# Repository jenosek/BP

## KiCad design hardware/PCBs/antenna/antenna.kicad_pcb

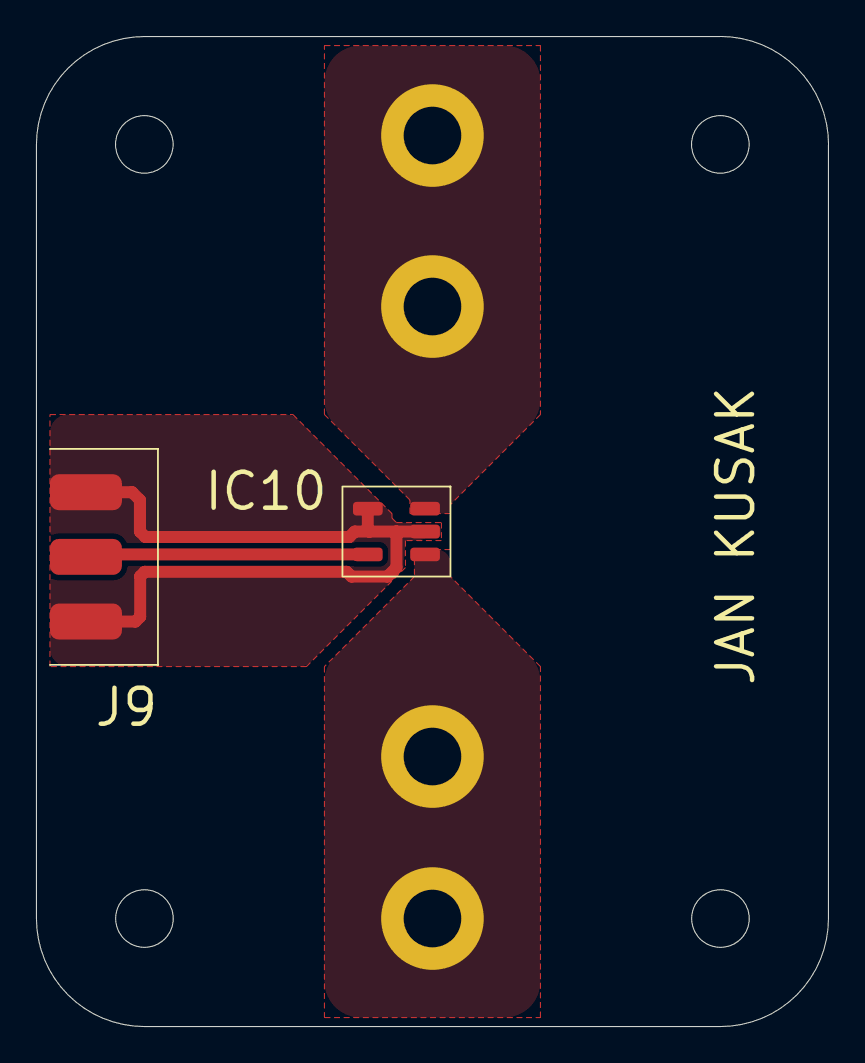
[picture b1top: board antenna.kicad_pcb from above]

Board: 2 copper layers, 44.0 x 55.0 mm, 10 parts (0 on the bottom side), 4 nets.

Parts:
H, H5, H6, H8: MountingHole; MountingHole_3.2mm_M3
H1, H2, H3, H4: MountingHole_Pad; MountingHole_3.2mm_M3_ISO7380_Pad
IC10: C1.5-52T+
J9: sma_diagonal

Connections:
GND: IC10.2 (SECONDARY_CT), IC10.4 (PRIMARY), J9.1 (GND), J9.3 (GND)
unnamed: IC10.6 (PRIMARY_DOT), J9.2 (SIGNAL)
unnamed: H3.1, H4.1, IC10.3 (SECONDARY)
unnamed: H1.1, H2.1, IC10.1 (SECONDARY_DOT)

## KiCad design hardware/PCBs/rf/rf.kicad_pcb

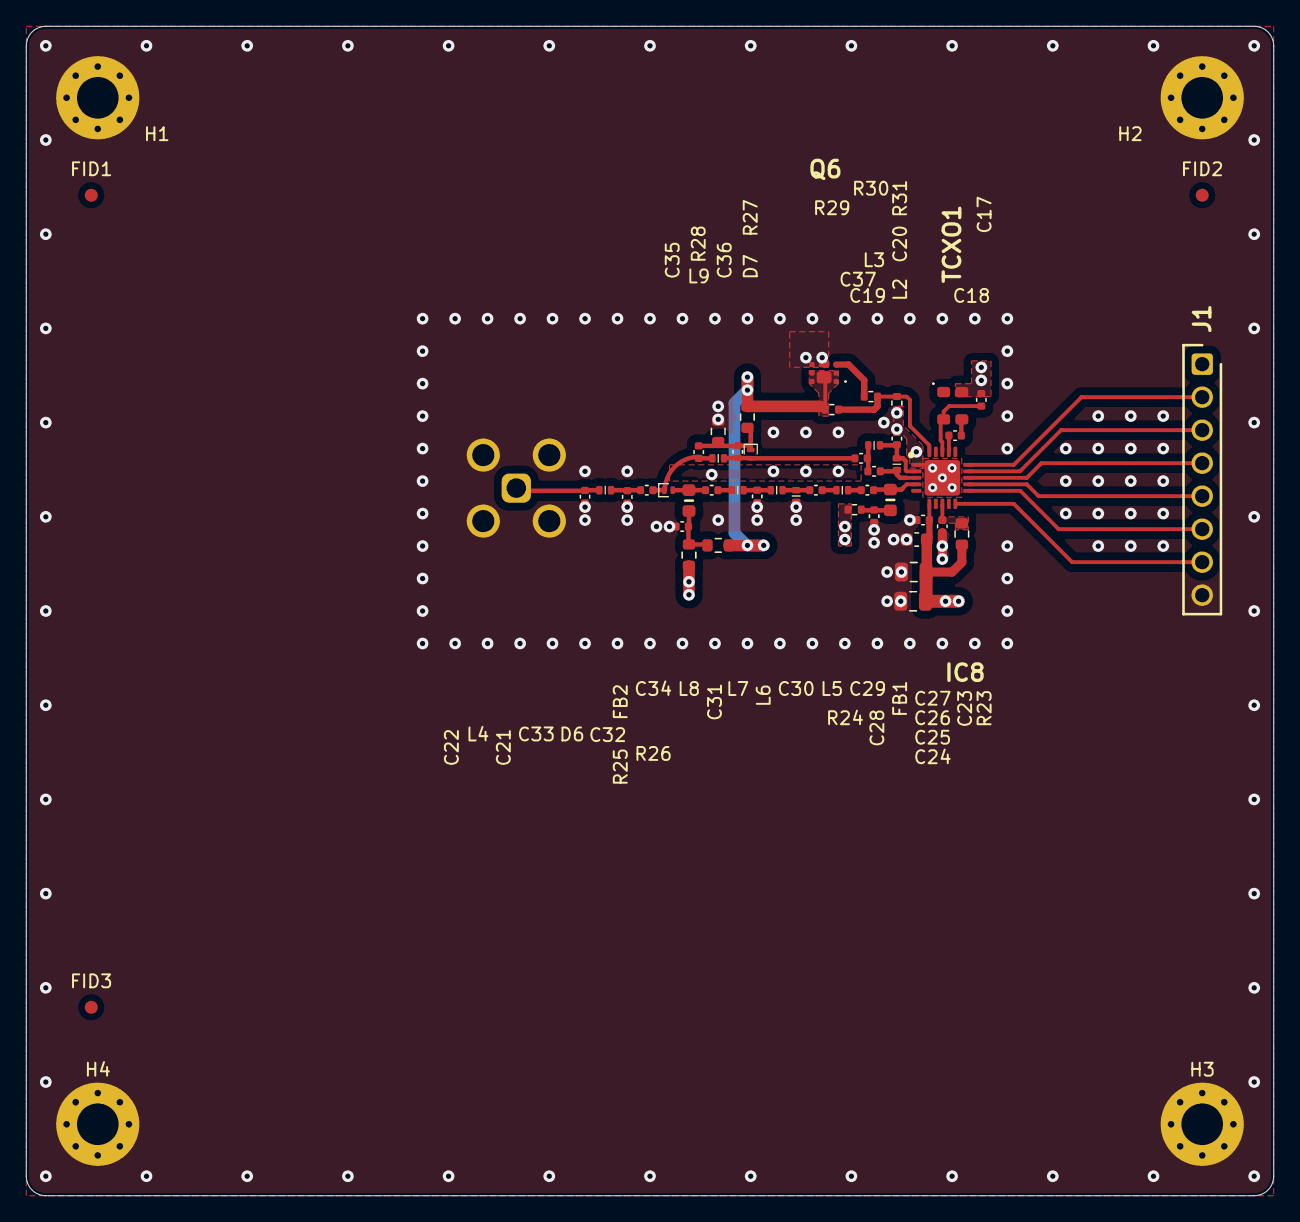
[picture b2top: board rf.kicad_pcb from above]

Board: 4 copper layers, 96.0 x 90.0 mm, 54 parts (1 on the bottom side), 32 nets.

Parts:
C17, C28, C32: 10n; C_0402_1005Metric
C18: 100p; C_0402_1005Metric
C19: 2p2; C_0402_1005Metric
C20: 4p7; C_0402_1005Metric
C21, C22, C35, C36: 8p8; C_0402_1005Metric
C23: 100n; C_0402_1005Metric
C24: 2u2; C_0805_2012Metric
C25: 100n; C_0805_2012Metric
C26: 100p; C_0603_1608Metric
C27: 33p; C_0402_1005Metric
C29: 7p5; C_0402_1005Metric
C30: 6p5; C_0402_1005Metric
C31: 7p3; C_0402_1005Metric
C33, C34, C37: 1n; C_0402_1005Metric
D6, D7: BAR63-02L-E6327; BAR6302LE6327
FB1, FB2: MMZ1608D241CTA00; BEADC1608X95N
FID1, FID2, FID3: Fiducial; Fiducial_1mm_Mask2mm
H1, H2, H3, H4: MountingHole_Pad; MountingHole_3.2mm_M3_Pad_Via
IC8: SI4468-A2A-IMR; QFN50P400X400X90-21N
J1: PH1-08-UA; HDRV8W64P0X254_1X8_2032X250X888P
J5: RFPC-SMA28-F; RFPCSMA28F
L2: 62n; LQW15CNR20J00B
L3: 56n; LQW15CNR20J00B
L4, L5, L9: 18n; LQW15CNR20J00B
L6, L7, L8: 20n; LQW15CNR20J00B
Q6: DMN1008UFDF-7; DMN1008UFDF7
R23, R26, R27, R28: 0; R_0603_1608Metric
R24: 178; R_0402_1005Metric
R25: 330; R_0603_1608Metric
R29, R30: 665; R_0402_1005Metric
R31: 100k; R_0402_1005Metric
TCXO1: TG2520SMN_30.000M-MCGNNM0; TG2520SMN30000MMCGNNM0

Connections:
+3V3: C17.1, C24.1, C25.1, C26.1, C27.1, IC8.6 (VDD_1), J1.1, R23.1, R24.1, R25.1, TCXO1.4 (VCC)
/ANT: C21.1, C33.1, L4.1
/COMMAND_DONE_RF: IC8.10 (GPIO1), J1.7
/GNDX: C17.2, IC8.18 (GND_1), TCXO1.2 (GND)
/Rx+: C20.2, IC8.2 (RXP), L2.2, L3.1
/Rx-: C19.1, IC8.3 (RXN), L2.1
/SCLK_RF: IC8.12 (SCLK), J1.5
/SDI_RF: IC8.14 (SDI), J1.3
/SDO_RF: IC8.13 (SDO), J1.4
/SW: Q6.1 (DRAIN_1), Q6.2 (DRAIN_2), Q6.5 (DRAIN_3), Q6.6 (DRAIN_4), Q6.7 (DRAIN_5), R26.1, R27.2, R29.1
/SW_MOS: IC8.20 (GPIO3), R29.2, R30.1, R31.1
/SW_Rx: C19.2, C37.2, L3.2
/SW_Tx: C34.2, L8.2
/Tx: C29.1, FB1.2, IC8.4 (TX)
/VDD2: C23.1, IC8.8 (VDD_2), R23.2
/XIN: C18.2, IC8.17 (XIN)
/nIRQ_RF: IC8.11 (NIRQ), J1.6
/nSEL_RF: IC8.15 (NSEL), J1.2
GND: C20.1, C21.2, C22.2, C23.2, C24.2, C25.2, C26.2, C27.2, C28.1, C31.1, C32.2, H1.1, H2.1, H3.1, H4.1, IC8.1 (SDN), IC8.21 (GND_2), J1.8, J5.2, J5.3, J5.4, J5.5, L6.2, Q6.4 (SOURCE_1), Q6.8 (SOURCE_2), R28.1, R31.2
unnamed: C22.1, J5.1, L4.2
unnamed: C28.2, FB1.1, R24.2
unnamed: C29.2, L5.1
unnamed: C30.1, L5.2
unnamed: C30.2, L6.1, L7.1
unnamed: C31.2, L7.2, L8.1
unnamed: C32.1, FB2.1, R25.2, R26.2
unnamed: C34.1, D6.2 (A), FB2.2
unnamed: C33.2, C35.1, D6.1 (K), L9.1
unnamed: C36.1, C37.1, D7.2 (A), L9.2
unnamed: C35.2, C36.2, D7.1 (K), R27.1, R28.2
unnamed: Q6.3 (GATE), R30.2
unnamed: C18.1, TCXO1.3 (OUT)

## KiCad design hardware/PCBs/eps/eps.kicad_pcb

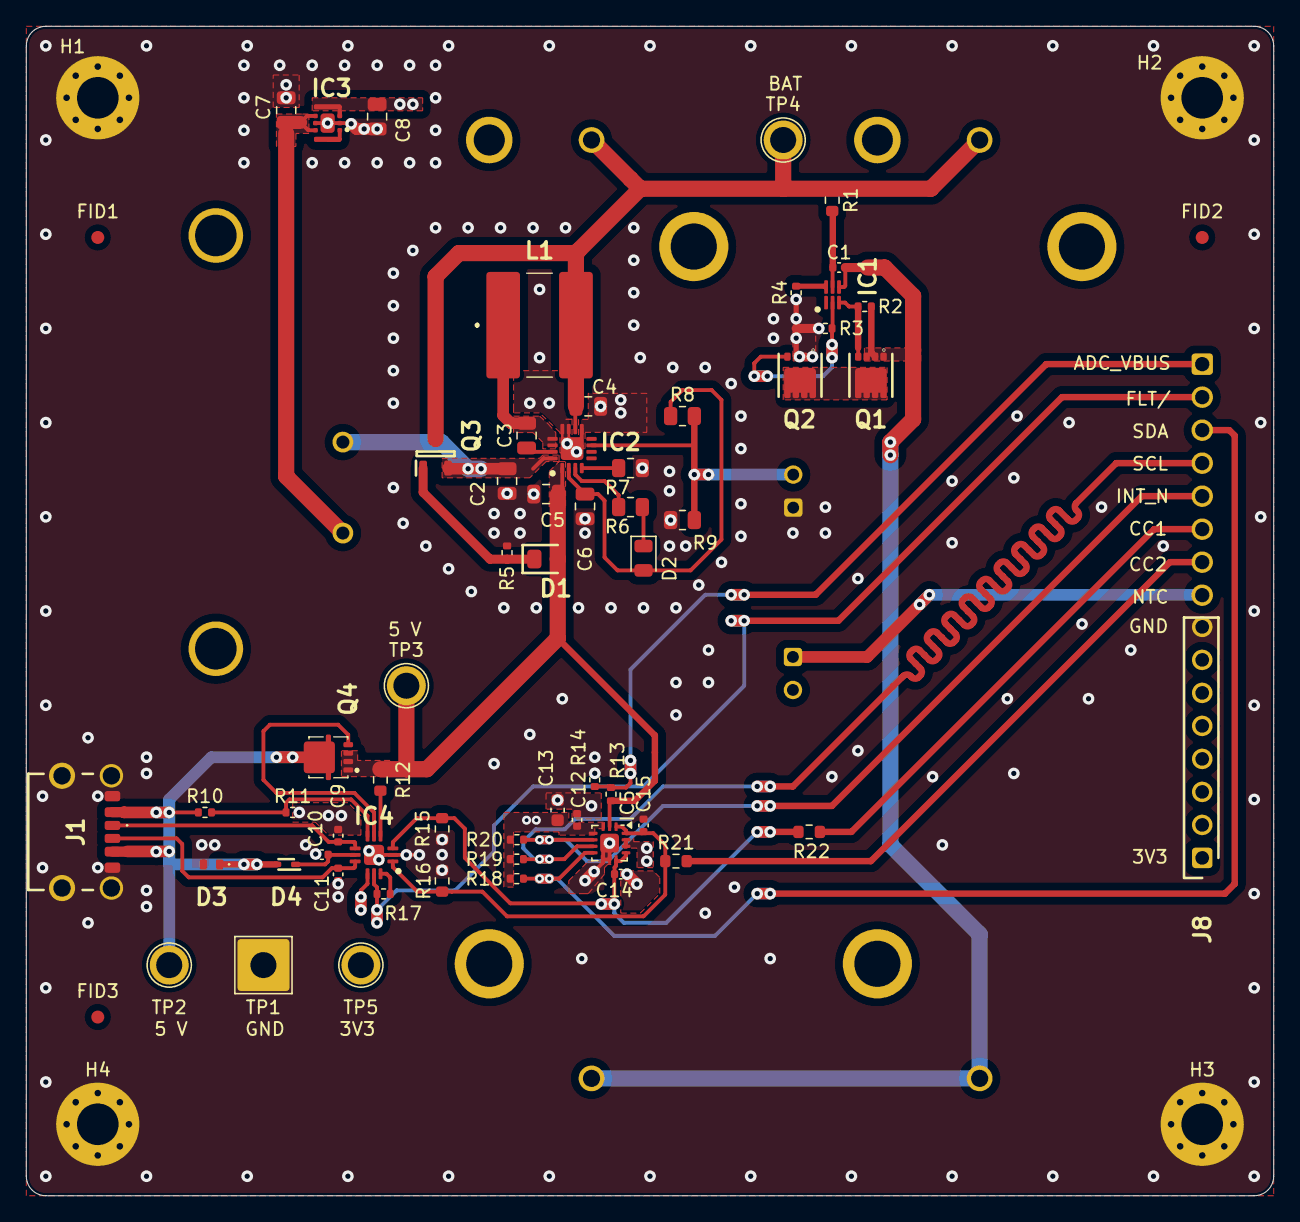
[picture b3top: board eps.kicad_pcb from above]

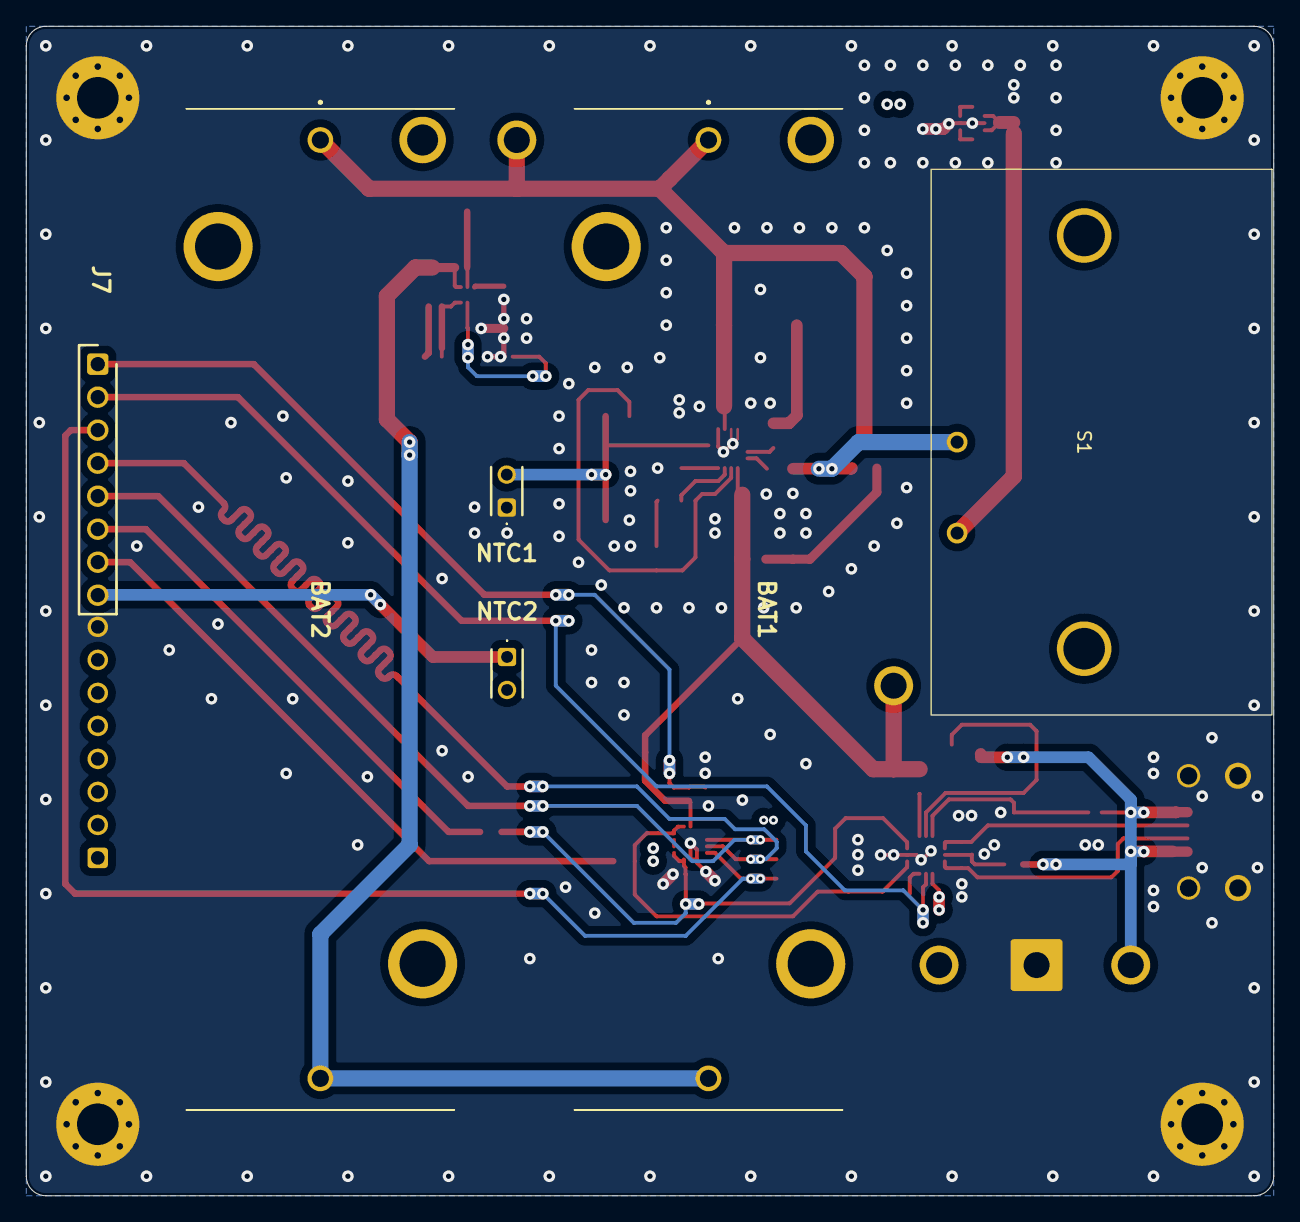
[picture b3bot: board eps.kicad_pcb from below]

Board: 4 copper layers, 96.0 x 90.0 mm, 71 parts (6 on the bottom side), 38 nets.

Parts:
BAT1, BAT2: 1043
C1, C10, C12: 100n; C_0402_1005Metric
C2, C4, C8: 10u; C_0805_2012Metric
C3: 47n; C_0805_2012Metric
C5, C6: 2u2; C_0805_2012Metric
C7: 4u7; C_0805_2012Metric
C9, C11, C14, C15: 330p; C_0402_1005Metric
C13: 1u; C_0603_1608Metric
D1: TS4148_RBG; DIOC2012X85N
D2: LED; LED_0805_2012Metric
D3: ESDA25P35-1U1M; ESDA25P351U1M
D4: BAT54KFILM; SODFL1608X70N
FID1, FID2, FID3: Fiducial; Fiducial_1mm_Mask2mm
H1, H2, H3, H4: MountingHole_Pad; MountingHole_3.2mm_M3_Pad_Via
IC1: BQ29732DSER; SON50P150X150X80-6N
IC2: BQ25302RTER; QFN50P300X300X80-17N-D
IC3: XCL240B333FR-G; XCL103D503CRG
IC4: TCPP01-M12; QFN50P300X300X100-13N-D
IC5: FUSB302BMPX; WQFN-14-1EP_2.5x2.5mm_P0.5mm_EP1.45x1.45mm
J1: UJC-H-G-SMT-2-P6-TR; UJCHGSMT2P6TR
J7: PH1-08-UA; HDRV8W64P0X254_1X8_2032X250X888P
J8: PRT-09279; RHDR8W87P0X254_1X8_2087X250X865P
L1: SRN8040-1R0Y; SRN80408R2Y
NTC1, NTC2: 103AT-2; 103AT2
Q1, Q2: CSD16406Q3; DQG_VSON-CLIP
Q3: DMP2305U-7; SOT96P240X115-3N
Q4: STL11N3LLH6; STL20N6F7
R1: 330; R_0603_1608Metric
R2, R3: 4M99; R_0402_1005Metric
R4: 2k2; R_0402_1005Metric
R5: 100k; R_0402_1005Metric
R6: 150; R_0805_2012Metric
R7: 20k; R_0805_2012Metric
R8: 4k53; R_0805_2012Metric
R9: 23k2; R_0805_2012Metric
R10, R17: 10k; R_0402_1005Metric
R11: 2k4; R_0402_1005Metric
R12, R21, R22: 0R; R_0603_1608Metric
R13: 1k69; R_0402_1005Metric
R14: 3k3; R_0402_1005Metric
R15, R16: 5k1; R_0603_1608Metric
R18, R19, R20: 4k7; R_0402_1005Metric
S1: RA12131100
TP1: TestPoint; TestPoint_THTPad_4.0x4.0mm_Drill2.0mm
TP2, TP3, TP4, TP5: TestPoint; TestPoint_Plated_Hole_D2.0mm

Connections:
+3V3: C8.1, C12.1, C13.1, IC3.3 (VOUT), IC3.8 (L2), IC4.10 (DB/), IC4.12 (VCC), IC5.3 (VDD), IC5.4 (VDD), IC5.12 (VCONN), IC5.13 (VCONN), J8.1, NTC2.2, R17.2, R18.1, R19.1, R20.1, TP5.1
/ADC_VBUS_PS: J7.1, R13.2, R14.1
/BYPASS_CC1_PS: J7.6, R22.2
/BYPASS_CC2_PS: J7.7, R21.2
/FLT/_PS: IC4.11 (FLT/), J7.2, R17.1
/INT_N_PS: IC5.5 (INT_N), J7.5, R20.2
/NTC_2_PS: J7.8, NTC2.1
/USB_CC1: C14.1, IC4.3 (CC1), IC5.10 (CC1), IC5.11 (CC1), R15.1, R22.1
/USB_CC2: C15.1, IC4.1 (CC2), IC5.1 (CC2), IC5.14 (CC2), R16.1, R21.1
/USB_SCL_PS: IC5.6 (SCL), J7.4, R19.2
/USB_SDA_PS: IC5.7 (SDA), J7.3, R18.2
/VBUS: C5.1, D1.2 (A), IC2.1 (VBUS), IC5.2 (VBUS), Q4.1 (S_1), Q4.2 (S_2), Q4.3 (S_3), R12.1, R13.1, TP3.1
GND: C2.2, C4.2, C5.2, C6.2, C7.2, C8.2, C9.1, C10.2, C11.2, C12.2, C13.2, C14.2, C15.2, D3.2 (A), H1.1, H2.1, H3.1, H4.1, IC2.9 (VSET), IC2.11 (GND_1), IC2.12 (GND_2), IC2.17 (EP), IC3.2 (AGND), IC3.5 (PGND), IC3.9 (EP), IC4.2 (GND), IC4.13 (EP), IC5.8 (GND), IC5.9 (GND), IC5.15 (GND), J1.1 (MH1), J1.2 (MH2), J1.3 (MH3), J1.4 (MH4), J1.A12 (GND_1), J1.B12 (GND_2), J8.8, NTC1.1, Q2.1 (S_1), Q2.2 (S_2), Q2.3 (S_3), R3.2, R4.2, R5.2, R7.2, R9.2, R11.2, R14.2, R15.2, R16.2, TP1.1
unnamed: BAT1.1 (+), BAT2.1 (+), C4.1, IC2.10 (BAT), L1.2, Q3.3 (D), R1.1, TP4.1
unnamed: BAT1.2 (-), BAT2.2 (-), C1.2, IC1.4 (VSS), Q1.1 (S_1), Q1.2 (S_2), Q1.3 (S_3), R2.2
unnamed: D1.1 (K), Q3.1 (G), R5.1
unnamed: C6.1, D2.2 (A), IC2.2 (REGN), R8.1
unnamed: D2.1 (K), R6.2
unnamed: D3.1 (K), D4.2 (A), J1.A9 (VBUS_1), J1.B9 (VBUS_2), Q4.5 (D), R10.1, TP2.1
unnamed: C10.1, D4.1 (K), IC4.8 (IN_GD)
unnamed: C1.1, IC1.5 (BAT), R1.2
unnamed: IC1.2 (COUT), Q2.4 (G), R3.1
unnamed: IC1.3 (DOUT), Q1.4 (G), R2.1
unnamed: IC1.6 (V-), R4.1
unnamed: C3.1, IC2.15 (BTST)
unnamed: IC2.4 (ICHG), R7.1
unnamed: C2.1, IC2.16 (PMID), Q3.2 (S), S1.1
unnamed: IC2.3 (STAT), R6.1
unnamed: C3.2, IC2.13 (SW_1), IC2.14 (SW_2), L1.1
unnamed: IC2.7 (TS), NTC1.2, R8.2, R9.1
unnamed: C7.1, IC3.4 (EN), IC3.6 (VIN), S1.2
unnamed: IC3.1 (LX), IC3.7 (L1)
unnamed: C9.2, IC4.7 (CC1C), J1.A5 (CC1)
unnamed: C11.1, IC4.9 (CC2C), J1.B5 (CC2)
unnamed: IC4.5 (GATE), Q4.4 (G)
unnamed: IC4.4 (SOURCE), R12.2
unnamed: IC4.6 (VBUS_CTRL), R10.2, R11.1
unnamed: Q1.5 (D_1), Q1.6 (D_2), Q1.7 (D_3), Q1.8 (D_4), Q1.9, Q2.5 (D_1), Q2.6 (D_2), Q2.7 (D_3), Q2.8 (D_4), Q2.9

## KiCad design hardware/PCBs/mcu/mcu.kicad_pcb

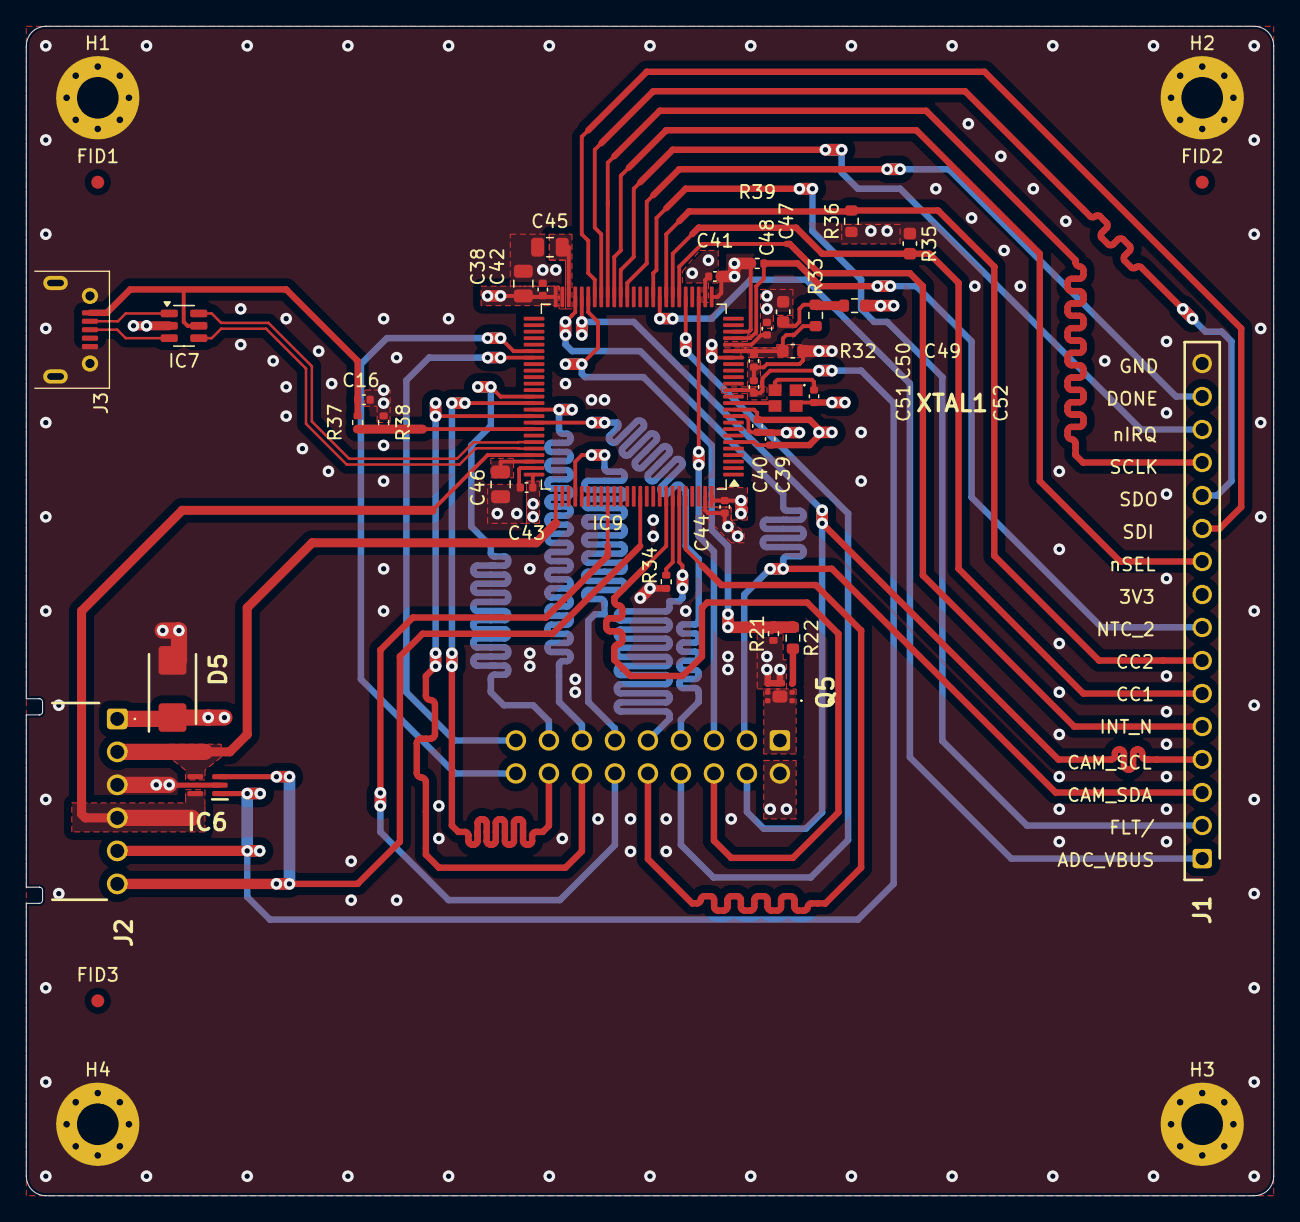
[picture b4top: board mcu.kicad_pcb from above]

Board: 4 copper layers, 96.0 x 90.0 mm, 43 parts (1 on the bottom side), 49 nets.

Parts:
C16, C39, C40, C41, C42, C43, C44, C48, C50, C51: 100n; C_0402_1005Metric
C38: 4u7; C_0805_2012Metric
C45, C46: 2u2; C_0805_2012Metric
C47, C49: 1u; C_0603_1608Metric
C52: 10n; C_0402_1005Metric
D5: SMLVT3V3; DIOM5436X265N
FID1, FID2, FID3: Fiducial; Fiducial_1mm_Mask2mm
H1, H2, H3, H4: MountingHole_Pad; MountingHole_3.2mm_M3_Pad_Via
IC6: ESDALC6V1W5; SOT65P210X110-5N
IC7: USBLC6-2SC6; SOT-23-6
IC9: STM32H7A3VIT6; LQFP-100_14x14mm_P0.5mm
J1: 61301611821; RHDR16W82P0X254_1X16_4114X250X865P
J2: 22-16-2060; 22162060
J3: MCR-B-S-RA-SMT-CS5A-NF-TR
J4: RS2-18-G; RHDR18W60P254_2X9_2337X500X889P
Q5: DMN1008UFDF-7; DMN1008UFDF7
R21: 100k; R_0402_1005Metric
R22: 169; R_0603_1608Metric
R32, R33, R36: 0R; R_0603_1608Metric
R34, R39: 10k; R_0402_1005Metric
R35: 0R; C_0603_1608Metric
R37: 1k69; R_0402_1005Metric
R38: 3k3; R_0402_1005Metric
XTAL1: ASDDV-8.000MHZ-LR-T; AbraconASDDV

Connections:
+3V3: C38.1, C39.1, C40.1, C41.1, C42.1, C43.1, C44.1, C52.1, D5.1 (K), IC9.6 (VBAT), IC9.11 (VDD), IC9.27 (VDD), IC9.50 (VDD), IC9.75 (VDD), IC9.100 (VDD), J1.9, J2.1, J4.2, R32.1, XTAL1.4 (VDD)
/3V3: J4.1, Q5.1 (DRAIN_1), Q5.2 (DRAIN_2), Q5.5 (DRAIN_3), Q5.6 (DRAIN_4), Q5.7 (DRAIN_5)
/ADC_VBUS: IC9.34 (PB0), J1.1
/BOOT: IC9.94 (BOOT0), R34.2
/CAM_3V3: IC9.45 (PE15), R21.1, R22.1
/CAM_SCL: IC9.46 (PB10), J1.4, J4.4
/CAM_SDA: IC9.47 (PB11), J1.3, J4.3
/CC1: IC9.32 (PC4), J1.6, R35.1
/CC2: IC9.33 (PC5), J1.7, R36.1
/COMMAND_DONE: IC9.39 (PE9), J1.15
/D0: IC9.63 (PC6), J4.15
/D1: IC9.64 (PC7), J4.16
/D2: IC9.65 (PC8), J4.13
/D3: IC9.66 (PC9), J4.14
/D4: IC9.79 (PC11), J4.11
/D5: IC9.84 (PD3), J4.12
/D6: IC9.95 (PB8), J4.9
/D7: IC9.96 (PB9), J4.10
/FLT/: IC9.35 (PB1), J1.2
/HS: IC9.28 (PA4), J4.5
/INT_N: IC9.31 (PA7), J1.5
/MCLK: IC9.67 (PA8), J4.7
/NRST: C51.1, IC6.1 (I/01), IC9.14 (NRST), J2.5
/NTC_2+: IC9.22 (PA0), J1.8, R39.2
/PCLK: IC9.30 (PA6), J4.8
/PWDN: IC9.57 (PD10), J4.17
/RCC_OSC_IN: IC9.12 (PH0), XTAL1.3 (OUTPUT)
/RST: IC9.56 (PD9), J4.18
/SCLK: IC9.42 (PE12), J1.13
/SDI: IC9.44 (PE14), J1.11
/SDO: IC9.43 (PE13), J1.12
/SWCLK: IC6.4 (I/03), IC9.76 (PA14), J2.2
/SWDIO: IC6.5 (I/04), IC9.72 (PA13), J2.4
/TRACE: IC6.3 (I/02), IC9.89 (PB3), J2.6
/USB_OTG_HS_D+: IC7.4 (I/O2), IC9.71 (PA12)
/USB_OTG_HS_D-: IC7.6 (I/O1), IC9.70 (PA11)
/USB_OTG_HS_VBUS: C16.2, IC7.5 (VBUS), J3.1 (VBUS), R37.1
/USB_VBUS: IC9.68 (PA9), R37.2, R38.1
/VCAP1: C45.1, IC9.48 (VCAP)
/VCAP2: C46.1, IC9.73 (VCAP)
/VDDA: C47.1, C48.1, IC9.21 (VDDA), R32.2, R33.2
/VREF+: C49.1, C50.1, IC9.20 (VREF+), R33.1
/VS: IC9.93 (PB7), J4.6
/nIRQ: IC9.40 (PE10), J1.14
/nSEL: IC9.41 (PE11), J1.10
GND: C16.1, C38.2, C39.2, C40.2, C41.2, C42.2, C43.2, C44.2, C45.2, C46.2, C47.2, C48.2, C49.2, C50.2, C51.2, C52.2, D5.2 (A), H1.1, H2.1, H3.1, H4.1, IC6.2 (GND), IC7.2 (GND), IC9.10 (VSS), IC9.19 (VSSA), IC9.23 (PA1), IC9.26 (VSS), IC9.49 (VSS), IC9.74 (VSS), IC9.99 (VSS), J1.16, J2.3, J3.5 (GND), J3.6 (Shield), Q5.4 (SOURCE_1), Q5.8 (SOURCE_2), R21.2, R34.1, R35.2, R36.2, R38.2, R39.1, XTAL1.2 (GND)
unnamed: IC7.3 (I/O2), J3.3 (D+)
unnamed: IC7.1 (I/O1), J3.2 (D-)
unnamed: Q5.3 (GATE), R22.2

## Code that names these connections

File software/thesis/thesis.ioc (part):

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Mcu.Name=STM32H7A3V(G-I)Tx
Mcu.Package=LQFP100
Mcu.UserName=STM32H7A3VITx
PA0.GPIOParameters=GPIO_Label
PA0.GPIO_Label=NTC_2+
PA0.Mode=IN16-Differential
PA0.Signal=ADC1_INP16
PA1.GPIOParameters=GPIO_Label
PA1.GPIO_Label=NTC_2-
PA1.Mode=IN16-Differential
PA1.Signal=ADC1_INN16
PA11.Mode=Device_Only_FS
PA11.Signal=USB_OTG_HS_DM
PA12.Mode=Device_Only_FS
PA12.Signal=USB_OTG_HS_DP
PA13.Mode=Trace_Asynchronous_SW
PA13.Signal=DEBUG_JTMS-SWDIO
PA14.Mode=Trace_Asynchronous_SW
PA14.Signal=DEBUG_JTCK-SWCLK
PA4.GPIOParameters=GPIO_Speed
PA4.GPIO_Speed=GPIO_SPEED_FREQ_VERY_HIGH
PA4.Mode=Slave_8_bits_External_Synchro
PA4.Signal=DCMI_HSYNC
PA6.GPIOParameters=GPIO_Speed
PA6.GPIO_Speed=GPIO_SPEED_FREQ_VERY_HIGH
PA6.Mode=Slave_8_bits_External_Synchro
PA6.Signal=DCMI_PIXCLK
PA7.GPIOParameters=GPIO_Label
PA7.GPIO_Label=INT_N
PA7.Signal=GPIO_Input
PA8.GPIOParameters=GPIO_Speed,GPIO_Label
PA8.GPIO_Label=DCMI_MCLK
PA8.GPIO_Speed=GPIO_SPEED_FREQ_VERY_HIGH
PA8.Mode=Clock-out-1
PA8.Signal=RCC_MCO_1
PA9.Mode=Activate_VBUS_FS
PA9.Signal=USB_OTG_HS_VBUS
PB0.GPIOParameters=GPIO_Label
PB0.GPIO_Label=ADC_VBUS
PB0.Signal=ADCx_INP9
PB1.GPIOParameters=GPIO_Label
PB1.GPIO_Label=FLT/
PB1.Signal=GPIO_Input
PB10.GPIOParameters=GPIO_Speed,GPIO_Pu
PB10.GPIO_Pu=GPIO_PULLUP
PB10.GPIO_Speed=GPIO_SPEED_FREQ_VERY_HIGH
PB10.Mode=I2C
PB10.Signal=I2C2_SCL
PB11.GPIOParameters=GPIO_Speed,GPIO_Pu
PB11.GPIO_Pu=GPIO_PULLUP
PB11.GPIO_Speed=GPIO_SPEED_FREQ_VERY_HIGH
PB11.Mode=I2C
PB11.Signal=I2C2_SDA
PB12.GPIOParameters=GPIO_Speed,GPIO_PuPd,GPIO_Label
PB12.GPIO_Label=SDN
PB12.GPIO_PuPd=GPIO_PULLDOWN
PB12.GPIO_Speed=GPIO_SPEED_FREQ_VERY_HIGH
PB12.Signal=GPIO_Output
PB3.Mode=Trace_Asynchronous_SW
PB3.Signal=DEBUG_JTDO-SWO
PB7.GPIOParameters=GPIO_Speed
PB7.GPIO_Speed=GPIO_SPEED_FREQ_VERY_HIGH
PB7.Mode=Slave_8_bits_External_Synchro
PB7.Signal=DCMI_VSYNC
PB8.GPIOParameters=GPIO_Speed
PB8.GPIO_Speed=GPIO_SPEED_FREQ_VERY_HIGH
PB8.Mode=Slave_8_bits_External_Synchro
PB8.Signal=DCMI_D6
PB9.GPIOParameters=GPIO_Speed
PB9.GPIO_Speed=GPIO_SPEED_FREQ_VERY_HIGH
PB9.Mode=Slave_8_bits_External_Synchro
PB9.Signal=DCMI_D7
PC11.GPIOParameters=GPIO_Speed
PC11.GPIO_Speed=GPIO_SPEED_FREQ_VERY_HIGH
PC11.Mode=Slave_8_bits_External_Synchro
PC11.Signal=DCMI_D4
PC4.GPIOParameters=GPIO_Label
PC4.GPIO_Label=CC1
PC4.Signal=ADCx_INP4
PC5.GPIOParameters=GPIO_Label
PC5.GPIO_Label=CC2
PC5.Signal=ADCx_INP8
PC6.GPIOParameters=GPIO_Speed
PC6.GPIO_Speed=GPIO_SPEED_FREQ_VERY_HIGH
PC6.Mode=Slave_8_bits_External_Synchro
PC6.Signal=DCMI_D0
PC7.GPIOParameters=GPIO_Speed
PC7.GPIO_Speed=GPIO_SPEED_FREQ_VERY_HIGH
PC7.Mode=Slave_8_bits_External_Synchro
PC7.Signal=DCMI_D1
PC8.GPIOParameters=GPIO_Speed
PC8.GPIO_Speed=GPIO_SPEED_FREQ_VERY_HIGH
PC8.Mode=Slave_8_bits_External_Synchro
PC8.Signal=DCMI_D2
PC9.GPIOParameters=GPIO_Speed
PC9.GPIO_Speed=GPIO_SPEED_FREQ_VERY_HIGH
PC9.Mode=Slave_8_bits_External_Synchro
PC9.Signal=DCMI_D3
PD10.GPIOParameters=GPIO_Speed,PinState,GPIO_Label
PD10.GPIO_Label=DCMI_PWDN
PD10.GPIO_Speed=GPIO_SPEED_FREQ_VERY_HIGH
PD10.PinState=GPIO_PIN_SET
PD10.Signal=GPIO_Output
PD3.GPIOParameters=GPIO_Speed
PD3.GPIO_Speed=GPIO_SPEED_FREQ_VERY_HIGH
PD3.Mode=Slave_8_bits_External_Synchro
PD3.Signal=DCMI_D5
PD9.GPIOParameters=GPIO_Speed,GPIO_Label
PD9.GPIO_Label=DCMI_RST
PD9.GPIO_Speed=GPIO_SPEED_FREQ_VERY_HIGH
PD9.Signal=GPIO_Output
PE10.GPIOParameters=GPIO_PuPd,GPIO_Label,GPIO_ModeDefaultEXTI
PE10.GPIO_Label=nIRQ
PE10.GPIO_ModeDefaultEXTI=GPIO_MODE_IT_FALLING
PE10.GPIO_PuPd=GPIO_NOPULL
PE10.Signal=GPXTI10
PE11.GPIOParameters=GPIO_Speed,GPIO_PuPd,GPIO_Label
PE11.GPIO_Label=SPI4_nSEL
PE11.GPIO_PuPd=GPIO_PULLUP
PE11.GPIO_Speed=GPIO_SPEED_FREQ_VERY_HIGH
PE11.Mode=NSS_Signal_Hard_Output
PE11.Signal=SPI4_NSS
PE12.GPIOParameters=GPIO_Speed
PE12.GPIO_Speed=GPIO_SPEED_FREQ_VERY_HIGH
PE12.Mode=Full_Duplex_Master
PE12.Signal=SPI4_SCK
PE13.GPIOParameters=GPIO_Speed,GPIO_PuPd
PE13.GPIO_PuPd=GPIO_NOPULL
PE13.GPIO_Speed=GPIO_SPEED_FREQ_VERY_HIGH
PE13.Mode=Full_Duplex_Master
PE13.Signal=SPI4_MISO
PE14.GPIOParameters=GPIO_Speed
PE14.GPIO_Speed=GPIO_SPEED_FREQ_VERY_HIGH
PE14.Mode=Full_Duplex_Master
PE14.Signal=SPI4_MOSI
PE15.GPIOParameters=GPIO_Label
PE15.GPIO_Label=DCMI_3V3
PE15.Signal=GPIO_Output
PE9.GPIOParameters=GPIO_Label
PE9.GPIO_Label=COMMAND_DONE
PE9.Signal=GPIO_Input
PH0-OSC_IN.Mode=HSE-External-Clock-Source
PH0-OSC_IN.Signal=RCC_OSC_IN
RCC.HSE_VALUE=8000000
RCC.SYSCLKFreq_VALUE=280000000
RCC.SYSCLKSource=RCC_SYSCLKSOURCE_PLLCLK
board=custom

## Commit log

2025-02-12 Crystal
2025-02-12 Structure changed
2025-02-15 USB-B micro added
2025-02-16 MCU finished. Beginning RF
2025-02-24 RF_Tx matched to 50ohms
2025-02-27 RF switch design begun
2025-02-27 Structure of repository changed
2025-02-28 Battery temperature meter added to MCU
2025-03-01 Done?
2025-03-01 0R added to RF supply
2025-03-03 Switch sim updated - final
2025-03-03 Board connector added
2025-03-03 Fixed MOS and board connector
2025-03-05 prevention save
2025-03-06 Revised and completed BOM
2025-03-07 Added symbol/model lib to files
2025-03-07 Additional models added
2025-03-07 EPS board started
2025-03-07 Libs merged
2025-03-07 Device change compability fixed
2025-03-09 EPS board created
2025-03-12 Draft of EPS PCB half-way done
2025-03-13 EPS pcb layout v0.1
2025-03-16 PCB-EPS 1/2
2025-03-16 EPS-PCB gnd fill reamaining
2025-03-20 PCB - EPS done. RF started
2025-03-21 RF finished
2025-03-23 PCB - RF done, 1/2 MCU
2025-03-23 ESP additional save
2025-03-27 Done? Rev.:1.2
2025-04-11 gitignore added
2025-04-11 ant. smooth corners
2025-04-12 SW added
2025-04-19 Ant done
2025-05-08 EPS programmed. Initial phase
2025-05-08 si4468 autoGen sw added (gpio included)
2025-05-11 preventive save - SPI halfway done
2025-05-17 RF's registers setup halfway done
2025-05-24 working on SPI opt.
2025-05-26 RF SPI working
2025-05-27 CAM problem
2025-05-29 FM working, data handling in progress
2025-05-30 Radio recognizes PING
2025-05-30 Meas. added, img progressing
2025-05-31 Matlab added
2025-06-01 MATLAB edited
